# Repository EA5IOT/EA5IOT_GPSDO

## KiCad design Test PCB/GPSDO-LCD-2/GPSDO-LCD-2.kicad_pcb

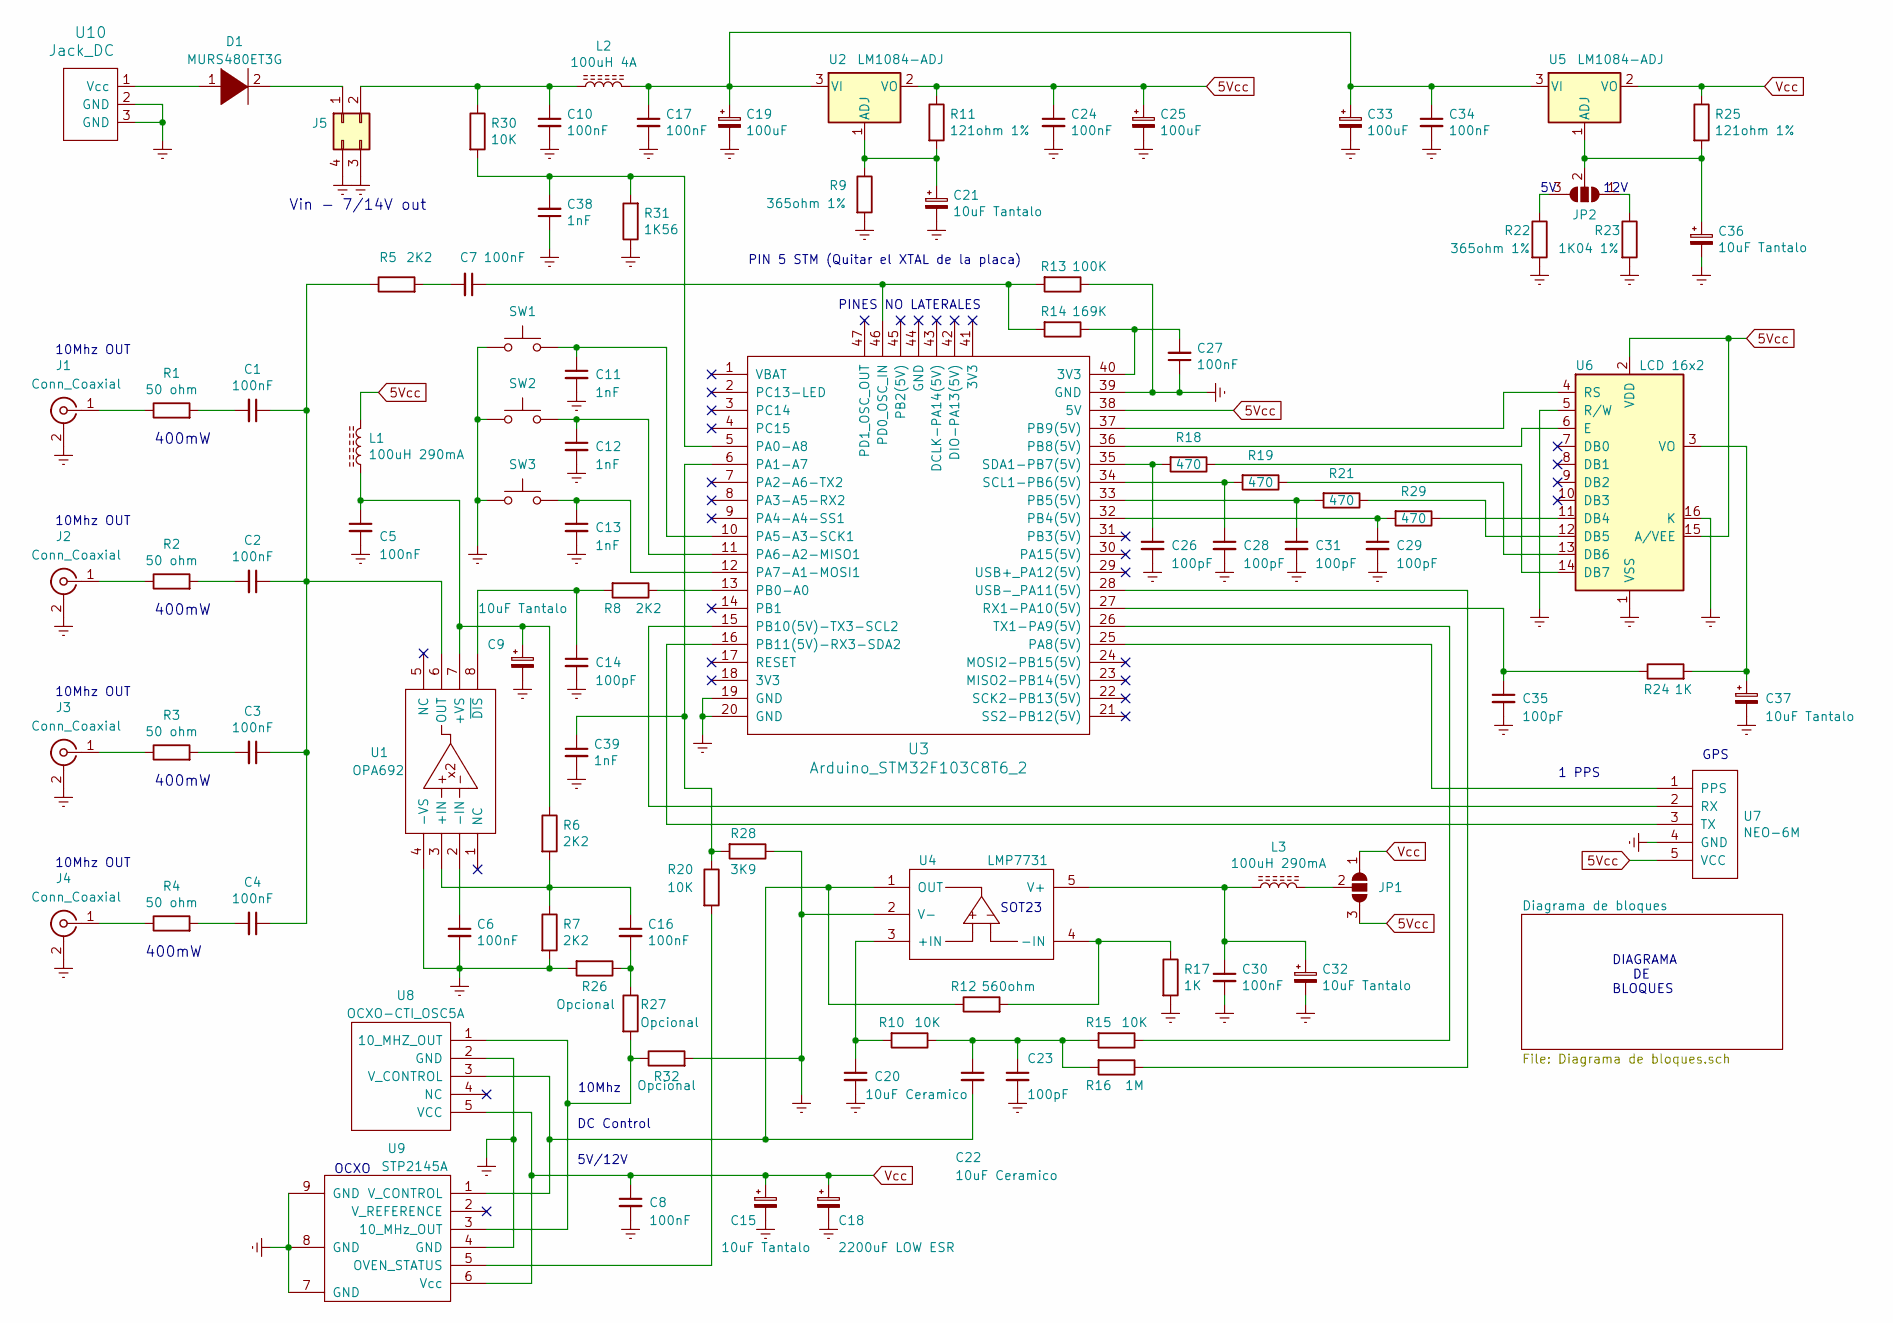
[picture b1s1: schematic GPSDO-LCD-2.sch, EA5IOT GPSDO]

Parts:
C1, C2, C3, C4, C5, C6, C7, C8, C10, C16, C17, C24, C27, C30, C34: 100nF; C_0805
C9, C15, C21, C32, C36, C37: 10uF Tantalo; CP_Tantalum_Case-C_EIA-6032-28_Wave
C11, C12, C13, C38, C39: 1nF; C_0805
C14, C23, C26, C28, C29, C31, C35: 100pF; C_0805
C18: 2200uF LOW ESR; CP_Elec_10x10
C19, C25, C33: 100uF; CP_Elec_6.3x5.8
C20, C22: 10uF Ceramico; C_0805
D1: MURS480ET3G; D_3220
J1, J2, J3, J4: Conn_Coaxial; SMA_THT_Jack_Straight
J5: Conn_02x02_Counter_Clockwise; SDL-104-X-XX_2x02
JP1, JP2: SolderJumper_3_Open; SolderJumper-3_P1.3mm_Open_RoundedPad1.0x1.5mm
L1, L3: 100uH 290mA; L_1210
L2: 100uH 4A; L_12x12mm_h6mm
R1, R2, R3, R4: 50 ohm; R_1206
R5, R6, R7, R8: 2K2; R_0805
R9, R22: 365ohm 1%; R_0805
R10, R15, R20, R30: 10K; R_0805
R11, R25: 121ohm 1%; R_0805
R12: 560ohm; R_0805
R13: 100K; R_0805
R14: 169K; R_0805
R16: 1M; R_0805
R17, R24: 1K; R_0805
R18, R19, R21, R29: 470; R_0805
R23: 1K04 1%; R_0805
R26, R27, R32: Opcional; R_0805
R28: 3K9; R_0805
R31: 1K56; R_0805
SW1, SW2, SW3: SW_Push; SW_PUSH_6mm_h13mm
U1: OPA692; SOIC-8-N
U2, U5: LM1084-ADJ; TO-220
U3: Arduino_STM32F103C8T6_2; Maple_Mini
U4: LMP7731; SOT-23-5
U6: LCD 16x2; WC1602A
U7: NEO-6M; GY-NEO6MV2
U8: OCXO-CTI_OSC5A; CIT_OSC5A
U9: STP2145A
U10: Jack_DC

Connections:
5Vcc: C24.1, C25.1, JP1.3 (B), L1.2, R11.1, U2.2 (VO), U3.38 (5V), U6.2 (VDD), U6.15 (A/VEE), U7.5 (VCC)
GNDREF: C5.2, C6.2, C8.2, C9.2, C10.2, C11.2, C12.2, C13.2, C14.2, C15.2, C17.2, C18.2, C19.2, C20.2, C21.2, C23.2, C24.2, C25.2, C26.2, C27.1, C28.2, C29.2, C30.2, C31.2, C32.2, C33.2, C34.2, C35.2, C36.2, C37.2, C38.1, C39.2, J1.2 (Ext), J2.2 (Ext), J3.2 (Ext), J4.2 (Ext), J5.3, J5.4, R7.2, R9.2, R13.1, R17.2, R22.2, R23.2, R26.2, R28.1, R31.1, R32.2, SW1.1, SW2.1, SW3.1, U1.4 (-VS), U3.19 (GND), U3.20 (GND), U3.39 (GND), U4.2 (V-), U6.1 (VSS), U6.5 (R/W), U6.16 (K), U7.4 (GND), U8.2 (GND), U9.4 (GND), U9.7 (GND), U9.8 (GND), U9.9 (GND), U10.2 (GND), U10.3 (GND)
unnamed: C1.1, C2.1, C3.1, C4.1, R5.1, U1.6 (OUT)
unnamed: C1.2, R1.2
unnamed: C2.2, R2.2
unnamed: C3.2, R3.2
unnamed: C4.2, R4.2
unnamed: C5.1, C9.1, L1.1, R6.1, U1.7 (+VS)
unnamed: C6.1, U1.2 (-IN)
unnamed: C7.1, R13.2, R14.2, U3.46 (PD0_OSC_IN)
unnamed: C7.2, R5.2
unnamed: C10.1, J5.2, L2.1, R30.1
unnamed: C11.1, SW1.2, U3.10 (PA5-A3-SCK1)
unnamed: C12.1, SW2.2, U3.11 (PA6-A2-MISO1)
unnamed: C13.1, SW3.2, U3.12 (PA7-A1-MOSI1)
unnamed: C14.1, R8.2, U1.8 (~DIS)
unnamed: C16.1, R6.2, R7.1, U1.3 (+IN)
unnamed: C16.2, R26.1, R27.1
unnamed: C17.1, C19.1, C33.1, C34.1, L2.2, U2.3 (VI), U5.3 (VI)
unnamed: C20.1, R10.2, U4.3 (+IN)
unnamed: C21.1, R9.1, R11.2, U2.1 (ADJ)
unnamed: C22.1, C23.1, R10.1, R15.2, R16.2
unnamed: C22.2, R12.1, U4.1 (OUT), U8.3 (V_CONTROL), U9.1 (V_CONTROL)
unnamed: C26.1, R18.2, U3.35 (SDA1-PB7(5V))
unnamed: C27.2, R14.1, U3.40 (3V3)
unnamed: C28.1, R19.2, U3.34 (SCL1-PB6(5V))
unnamed: C29.1, R29.2, U3.32 (PB4(5V))
unnamed: C30.1, C32.1, L3.1, U4.5 (V+)
unnamed: C31.1, R21.2, U3.33 (PB5(5V))
unnamed: C35.1, R24.1, U3.27 (RX1-PA10(5V))
unnamed: C36.1, JP2.2 (C), R25.2, U5.1 (ADJ)
unnamed: C37.1, R24.2, U6.3 (VO)
unnamed: C38.2, R30.2, R31.2, U3.5 (PA0-A8)
unnamed: C39.1, R20.1, R28.2, U3.6 (PA1-A7)
unnamed: D1.1 (K), U10.1 (Vcc)
unnamed: D1.2 (A), J5.1
unnamed: J1.1 (In), R1.1
unnamed: J2.1 (In), R2.1
unnamed: J3.1 (In), R3.1
unnamed: J4.1 (In), R4.1
unnamed: JP1.2 (C), L3.2
unnamed: JP2.1 (A), R23.1
unnamed: JP2.3 (B), R22.1
unnamed: R8.1, U3.13 (PB0-A0)
unnamed: R12.2, R17.1, U4.4 (-IN)
unnamed: R15.1, U3.26 (TX1-PA9(5V))
unnamed: R16.1, U3.28 (USB-_PA11(5V))
unnamed: R18.1, U6.14 (DB7)
unnamed: R19.1, U6.13 (DB6)
unnamed: R20.2, U9.5 (OVEN_STATUS)
unnamed: R21.1, U6.12 (DB5)
unnamed: R27.2, R32.1, U8.1 (10_MHZ_OUT), U9.3 (10_MHz_OUT)
unnamed: R29.1, U6.11 (DB4)
unnamed: U3.15 (PB10(5V)-TX3-SCL2), U7.2 (RX)
unnamed: U3.16 (PB11(5V)-RX3-SDA2), U7.3 (TX)
unnamed: U3.25 (PA8(5V)), U7.1 (PPS)
unnamed: U3.36 (PB8(5V)), U6.6 (E)
unnamed: U3.37 (PB9(5V)), U6.4 (RS)
Vcc: C8.1, C15.1, C18.1, JP1.1 (A), R25.1, U5.2 (VO), U8.5 (VCC), U9.6 (Vcc)

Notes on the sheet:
GPS
10Mhz OUT
1 PPS
PIN 5 STM (Quitar el XTAL de la placa)
10Mhz
OCXO
DC Control
12V
SOT23
5V/12V
PINES NO LATERALES
DIAGRAMA DE BLOQUES
400mW
Vin - 7/14V out

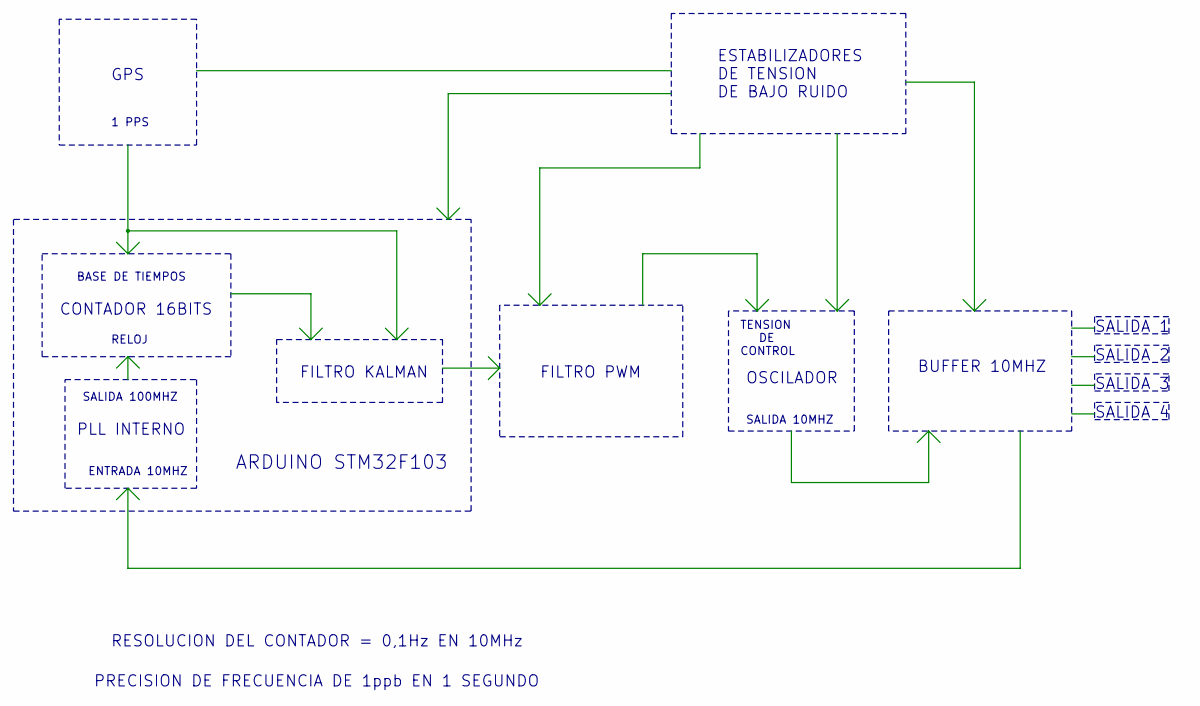
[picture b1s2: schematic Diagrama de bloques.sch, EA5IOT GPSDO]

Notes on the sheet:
FILTRO PWM
OSCILADOR
SALIDA 10MHZ
TENSION DE CONTROL
BUFFER 10MHZ
CONTADOR 16BITS
FILTRO KALMAN
PLL INTERNO
ENTRADA 10MHZ
SALIDA 100MHZ
RELOJ
BASE DE TIEMPOS
GPS
1 PPS
ARDUINO STM32F103
ESTABILIZADORES DE TENSION DE BAJO RUIDO
SALIDA 1
SALIDA 2
SALIDA 3
SALIDA 4
RESOLUCION DEL CONTADOR = 0,1Hz EN 10MHz
PRECISION DE FRECUENCIA DE 1ppb EN 1 SEGUNDO

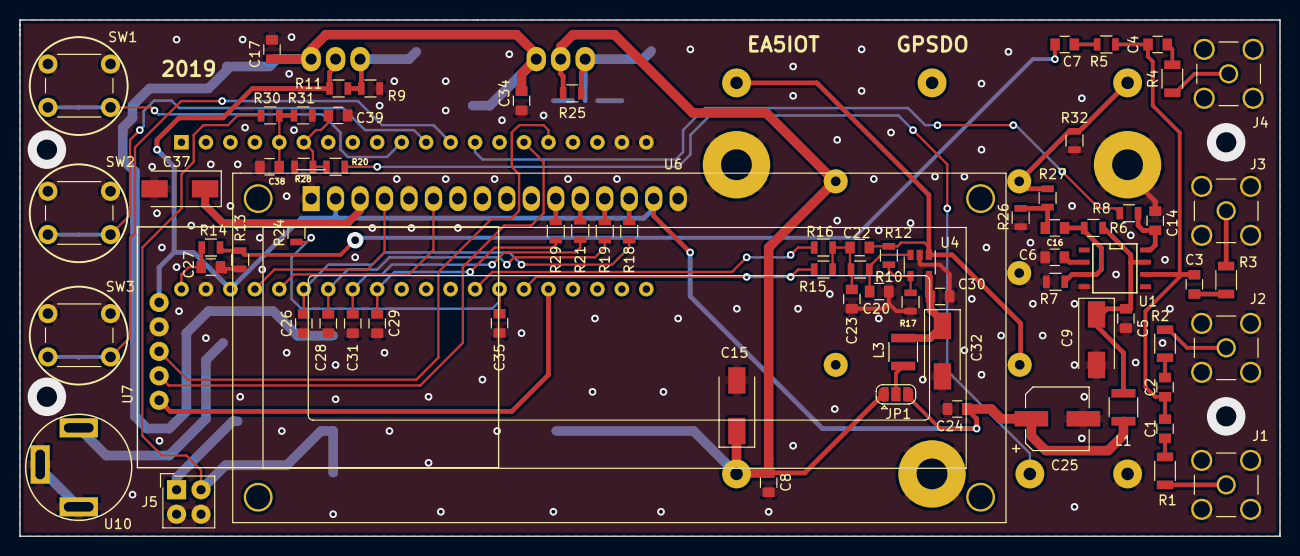
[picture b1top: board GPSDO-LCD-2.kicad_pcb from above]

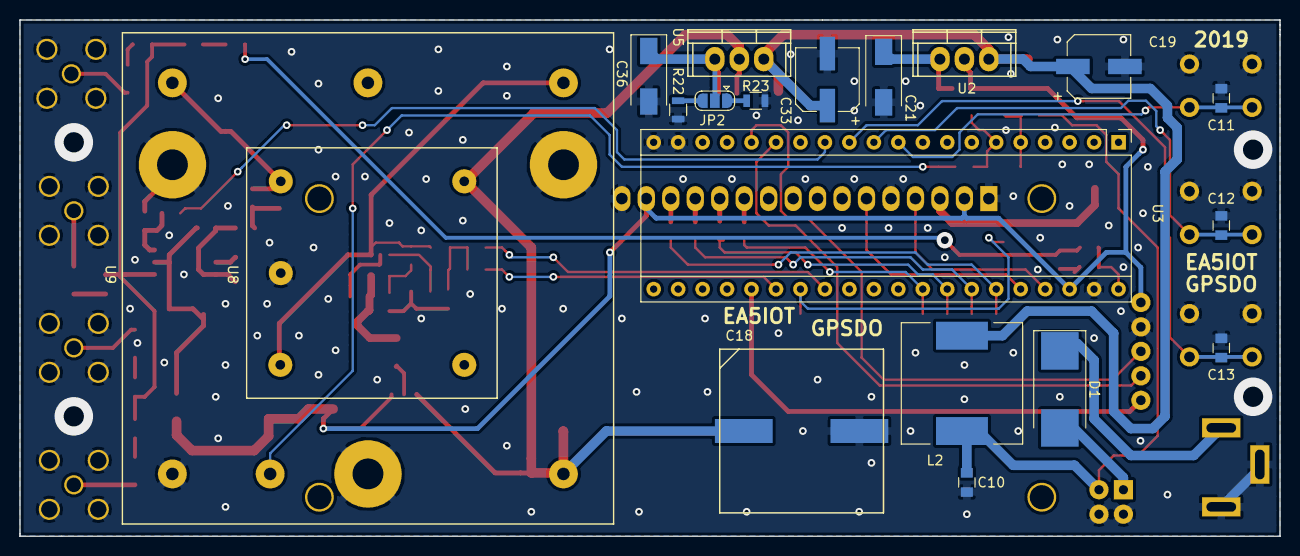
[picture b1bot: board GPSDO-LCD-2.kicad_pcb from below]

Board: 2 copper layers, 130.8 x 53.6 mm, 95 parts (19 on the bottom side), 59 nets.

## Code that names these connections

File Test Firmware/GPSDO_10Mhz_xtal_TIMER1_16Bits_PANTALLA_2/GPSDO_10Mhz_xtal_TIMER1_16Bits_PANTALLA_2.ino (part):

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// PATAS Microcontrolador
//      TX2         PA2															                            // TX RS232 PC (al RX del PC)
//		  RX2		      PA3															                            // RX RS232 PC (al TX del PC)
//      TX3         PB10															                          // TX GPS (al RX del GPS), cable verde
// 		  RX3		      PB11															                          // RX GPS (al TX del GPS), cable blanco

#define Timer1Ch1   PA8                                                         // Señal de 1PPS del gps (Activa cuando el GPS está enganchado), cable naranja
#define Timer1Ch2   PA9                                                         // Salida PWM Control de Frecuencia
#define Timer1Ch3   PA10															                          // Salida PWM contraste pantalla, cable verde pata 3 Pantalla
#define OcxoGain    50.0

#define RS		      PB9															                            // Pin 4 pantalla, cable blanco
//#define RW              																                      // Pin 5 (a masa directamente, no se usa y así evitamos poner los conversores de 5 a 3,3V)
#define EN		      PB8															                            // Pin 6 pantalla, cable amarillo
#define DB7		      PB7															                            // Pin 14 pantalla, cable azul
#define DB6		      PB6															                            // Pin 13 pantalla, cable naranja
#define DB5		      PB5															                            // Pin 12 pantalla, cable marron
#define DB4 	      PB4 														                            // Pin 11 pantalla, cable violeta

#define E1		      PA7															                            // Pin 1 encoder/pulsador
#define E2          PA6															                            // Pin 2 encoder/pulsador
#define EP          PA5															                            // Pin pulsador encoder/pulsador

#define VIN         PA0                                                         // Entrada tensión de alimentación
#define OvenStatus  PA1                                                         // Entrada Oven Status

#define OutEN       PB0                                                         // Control de la señal de salida

#define LED         PC13                                                        // LED pata PC13
//
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
  // Input Compare en CH1 (1pps GPS)
  pinMode(Timer1Ch1, INPUT);
  TIMER1->regs.gen->CCMR1 = 0x0001;                                             // Input Capture Channel 1 mapped to TI1->PA8
  TIMER1->regs.gen->CCER  = 0x0001;                                             // Input Capture Enable, Timer1_Channel1 rising edge on TI1->PA8 para el 1PPS del GPS
  TIMER1->regs.gen->DIER  = 0x0007;                                             // Se activan las interrupciones de Update, Input Capture1 y Output Compare2
  TIMER1->regs.gen->PSC   = 0x0000;                                             // Hay que poner un cero en el preescaler del TIMER1 para que cuente a 100Mhz, porque las librerias lo arrancan a 2

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  TIMER1->regs.gen->CCR2  = 0x8000;                                             // PWM al 50%

  GPIOA->regs->CRH &= 0xFFFFFF3F;                                             	// Se hace un and para poner los ceros
  //GPIOA->regs->CRH |= 0x000000C0;                                             // Se hace un or para poner los unos, alternate function open drain PA9 para PWM de 5V    
  GPIOA->regs->CRH   |= 0x00000080;                                             // Se hace un or para poner los unos, alternate function push-pull PA9 para PWM de 3,3V

  // PWM en CH3
  TIMER1->regs.gen->CCMR2 |= 0x0068;                                            // Output Compare CH3
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
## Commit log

2019-04-28 Updates README.md
    Auto commit by GitBook Editor
2019-04-28 EA5IOT_GPSDO
    EA5IOT_GPSDO
2019-06-19 Update
    Update
2019-06-21 LPF_10MHZ_V2
    LPF_10MHZ_V2
2019-06-30 FLL Update
    FLL Update
2019-09-10 Correccion pin CLK MCU
    Correccion pin CLK MCU
2019-09-12 Update GPSDO_10Mhz_xtal_TIMER1_16Bits_PANTALLA_2.ino
    Speed Lock
2019-09-29 Version Mini
    Version Mini
2019-09-30 Buffer update
    Buffer update
2019-10-10 Version Doble
    Version Doble
2020-01-10 U4 Update
    U4 Update

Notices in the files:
Test Firmware/GPSDO_10Mhz_xtal_TIMER1_16Bits_PANTALLA_2/GPSDO_10Mhz_xtal_TIMER1_16Bits_PANTALLA_2.ino:
Copyright (C) 2020
This program is free software: you can redistribute it and/or modify
it under the terms of the GNU General Public License as published by
the Free Software Foundation, either version 3 of the License, or
(at your option) any later version.
